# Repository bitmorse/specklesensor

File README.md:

# specklesensor
A photodiode array for laser speckle sensing and vibrometry.

Read the full paper [here](docs/thesis.pdf).

Spectral analysis of a 133 Hz surface vibration under different laser configurations. Top: Power spectral density showing the target frequency
component. Bottom: SNR improvement with increasing number of active lasers:

## RPI Camera Bench Setup

Side by side comparison of the speckle pattern captured by a Raspberry Pi camera with
one red laser

and three red lasers.

## Laser setups

## Hardware
The PCBs used for the experiments are in the `hardware` folder. The PCBs are designed using KiCad, an open source schematics and layout editor. The PCBs were manufactured by JLCPCB and hand assembled using hot air reflow.

- `speckle_pcb_rev1`: The 3x3 photodiode array.
- `speckle_amp_pcb_rev1`: The amplifier PCB for 3x3 array.

Careful attention must be paid to cleaning the PCBs after soldering, as any residue flux can lead to leakage currents and noise in the measurements.

## Scripts
- `emulations`: The script to process camera frames to CSV files for emulating the photodiode array. A notebook provides the signal processing.
- `waveshare`: Scripts for testing the first ADC.
- `daqhat`: Scripts for testing the second ADC and data from the multi-laser experiment.

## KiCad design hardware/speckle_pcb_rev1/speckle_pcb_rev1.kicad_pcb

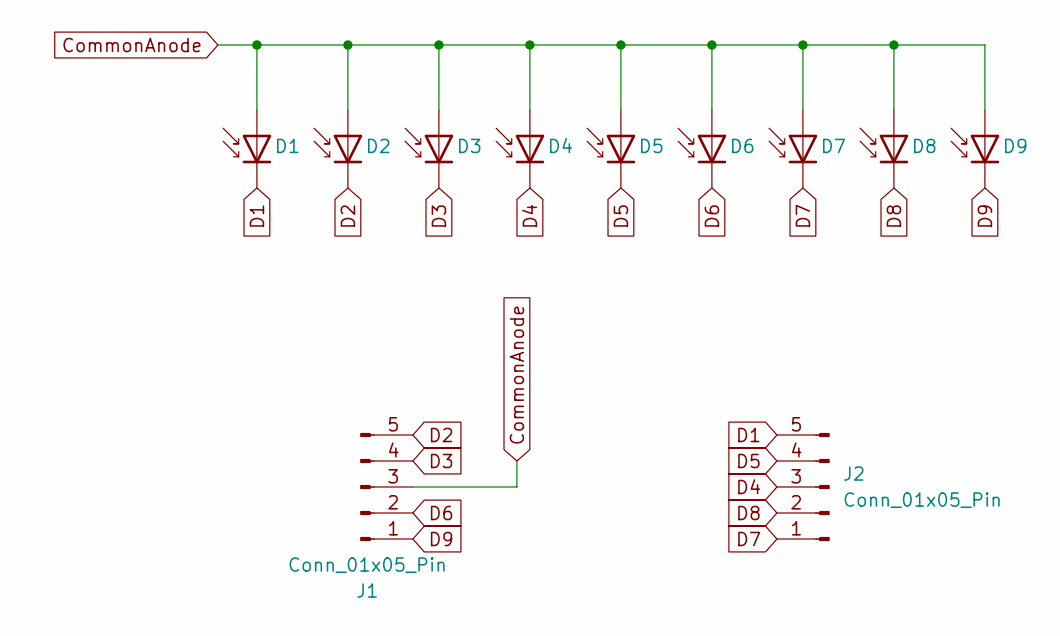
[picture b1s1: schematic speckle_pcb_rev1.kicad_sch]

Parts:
D1, D2, D3, D4, D5, D6, D7, D8, D9: D_Photo; VEMD2704
J1, J2: Conn_01x05_Pin; PinHeader_1x05_P1.27mm_Vertical

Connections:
CommonAnode: D1.2 (A), D2.2 (A), D3.2 (A), D4.2 (A), D5.2 (A), D6.2 (A), D7.2 (A), D8.2 (A), D9.2 (A), J1.3
D1: D1.1 (K), J2.5
D2: D2.1 (K), J1.5
D3: D3.1 (K), J1.4
D4: D4.1 (K), J2.3
D5: D5.1 (K), J2.4
D6: D6.1 (K), J1.2
D7: D7.1 (K), J2.1
D8: D8.1 (K), J2.2
D9: D9.1 (K), J1.1

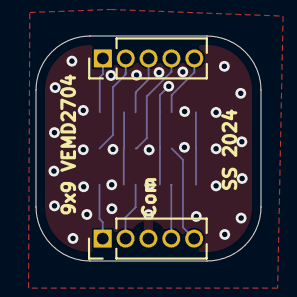
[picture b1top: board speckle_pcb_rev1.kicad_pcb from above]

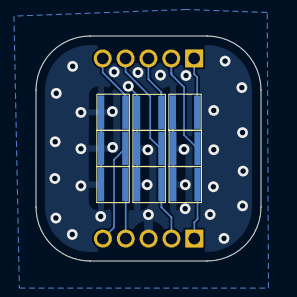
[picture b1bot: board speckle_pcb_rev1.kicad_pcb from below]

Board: 2 copper layers, 12.5 x 12.5 mm, 11 parts (9 on the bottom side), 10 nets.

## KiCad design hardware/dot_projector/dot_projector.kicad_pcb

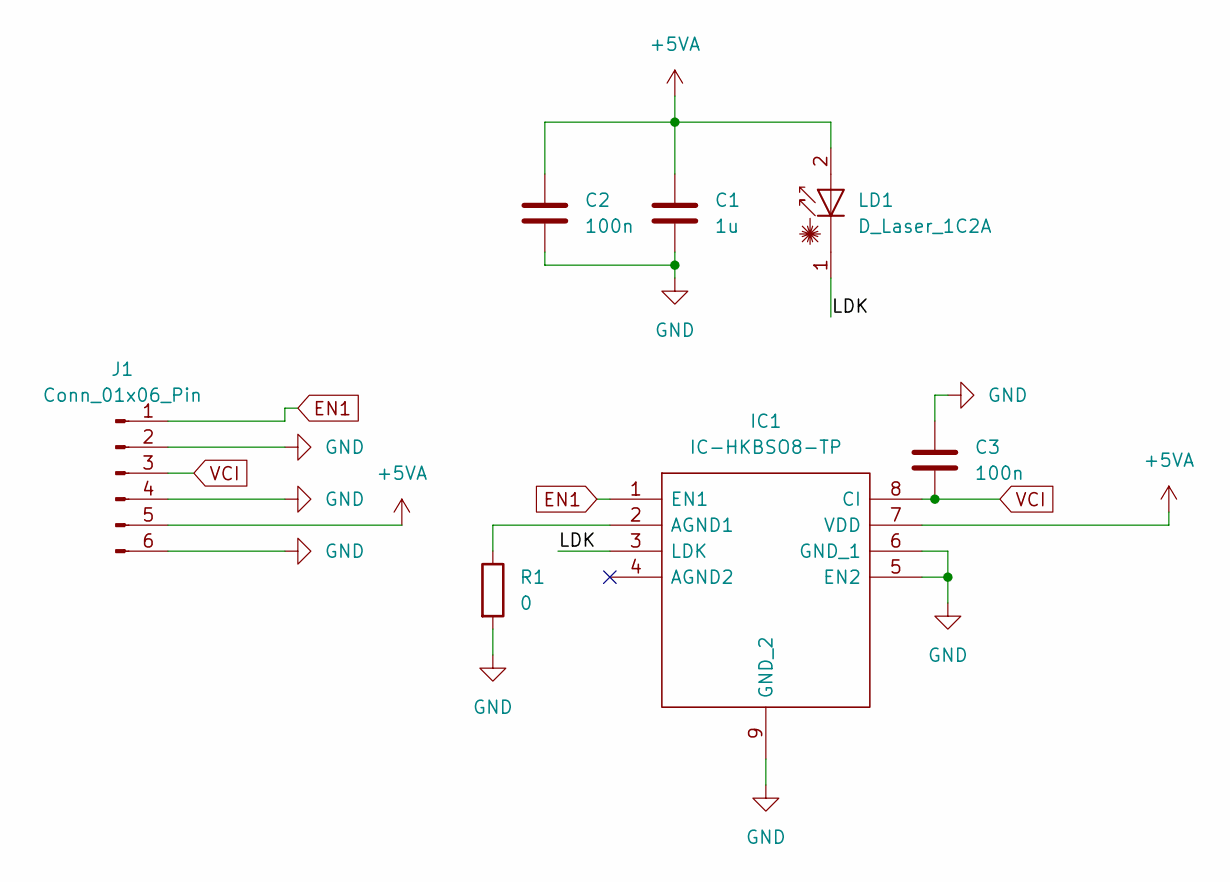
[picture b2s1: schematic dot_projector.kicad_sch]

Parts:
C1: 1u; C_0603_1608Metric
C2, C3: 100n; C_0603_1608Metric
IC1: IC-HKBSO8-TP; SOIC127P600X148-9N; Manufacturer_Part_Number IC-HKBSO8-TP
J1: Conn_01x06_Pin; PinHeader_1x06_P1.27mm_Vertical
LD1: D_Laser_1C2A; ams_belago1.1
R1: 0; R_0603_1608Metric

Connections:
+5VA: C1.1, C2.1, IC1.7 (VDD), J1.5, LD1.2 (A)
/LDK: IC1.3 (LDK), LD1.1 (K)
EN1: IC1.1 (EN1), J1.1
GND: C1.2, C2.2, C3.1, IC1.5 (EN2), IC1.6 (GND_1), IC1.9 (GND_2), J1.2, J1.4, J1.6, R1.2
unnamed: IC1.2 (AGND1), R1.1
VCI: C3.2, IC1.8 (CI), J1.3

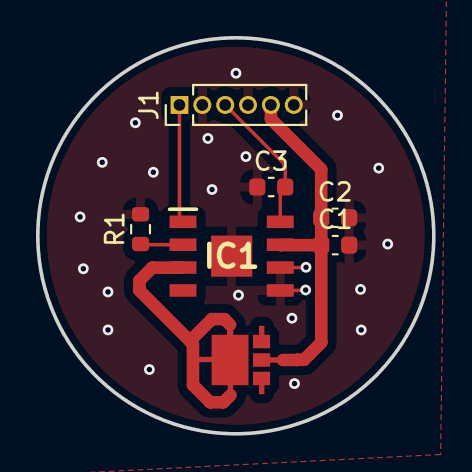
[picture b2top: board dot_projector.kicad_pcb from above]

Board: 2 copper layers, 22.0 x 22.0 mm, 7 parts (0 on the bottom side), 6 nets.

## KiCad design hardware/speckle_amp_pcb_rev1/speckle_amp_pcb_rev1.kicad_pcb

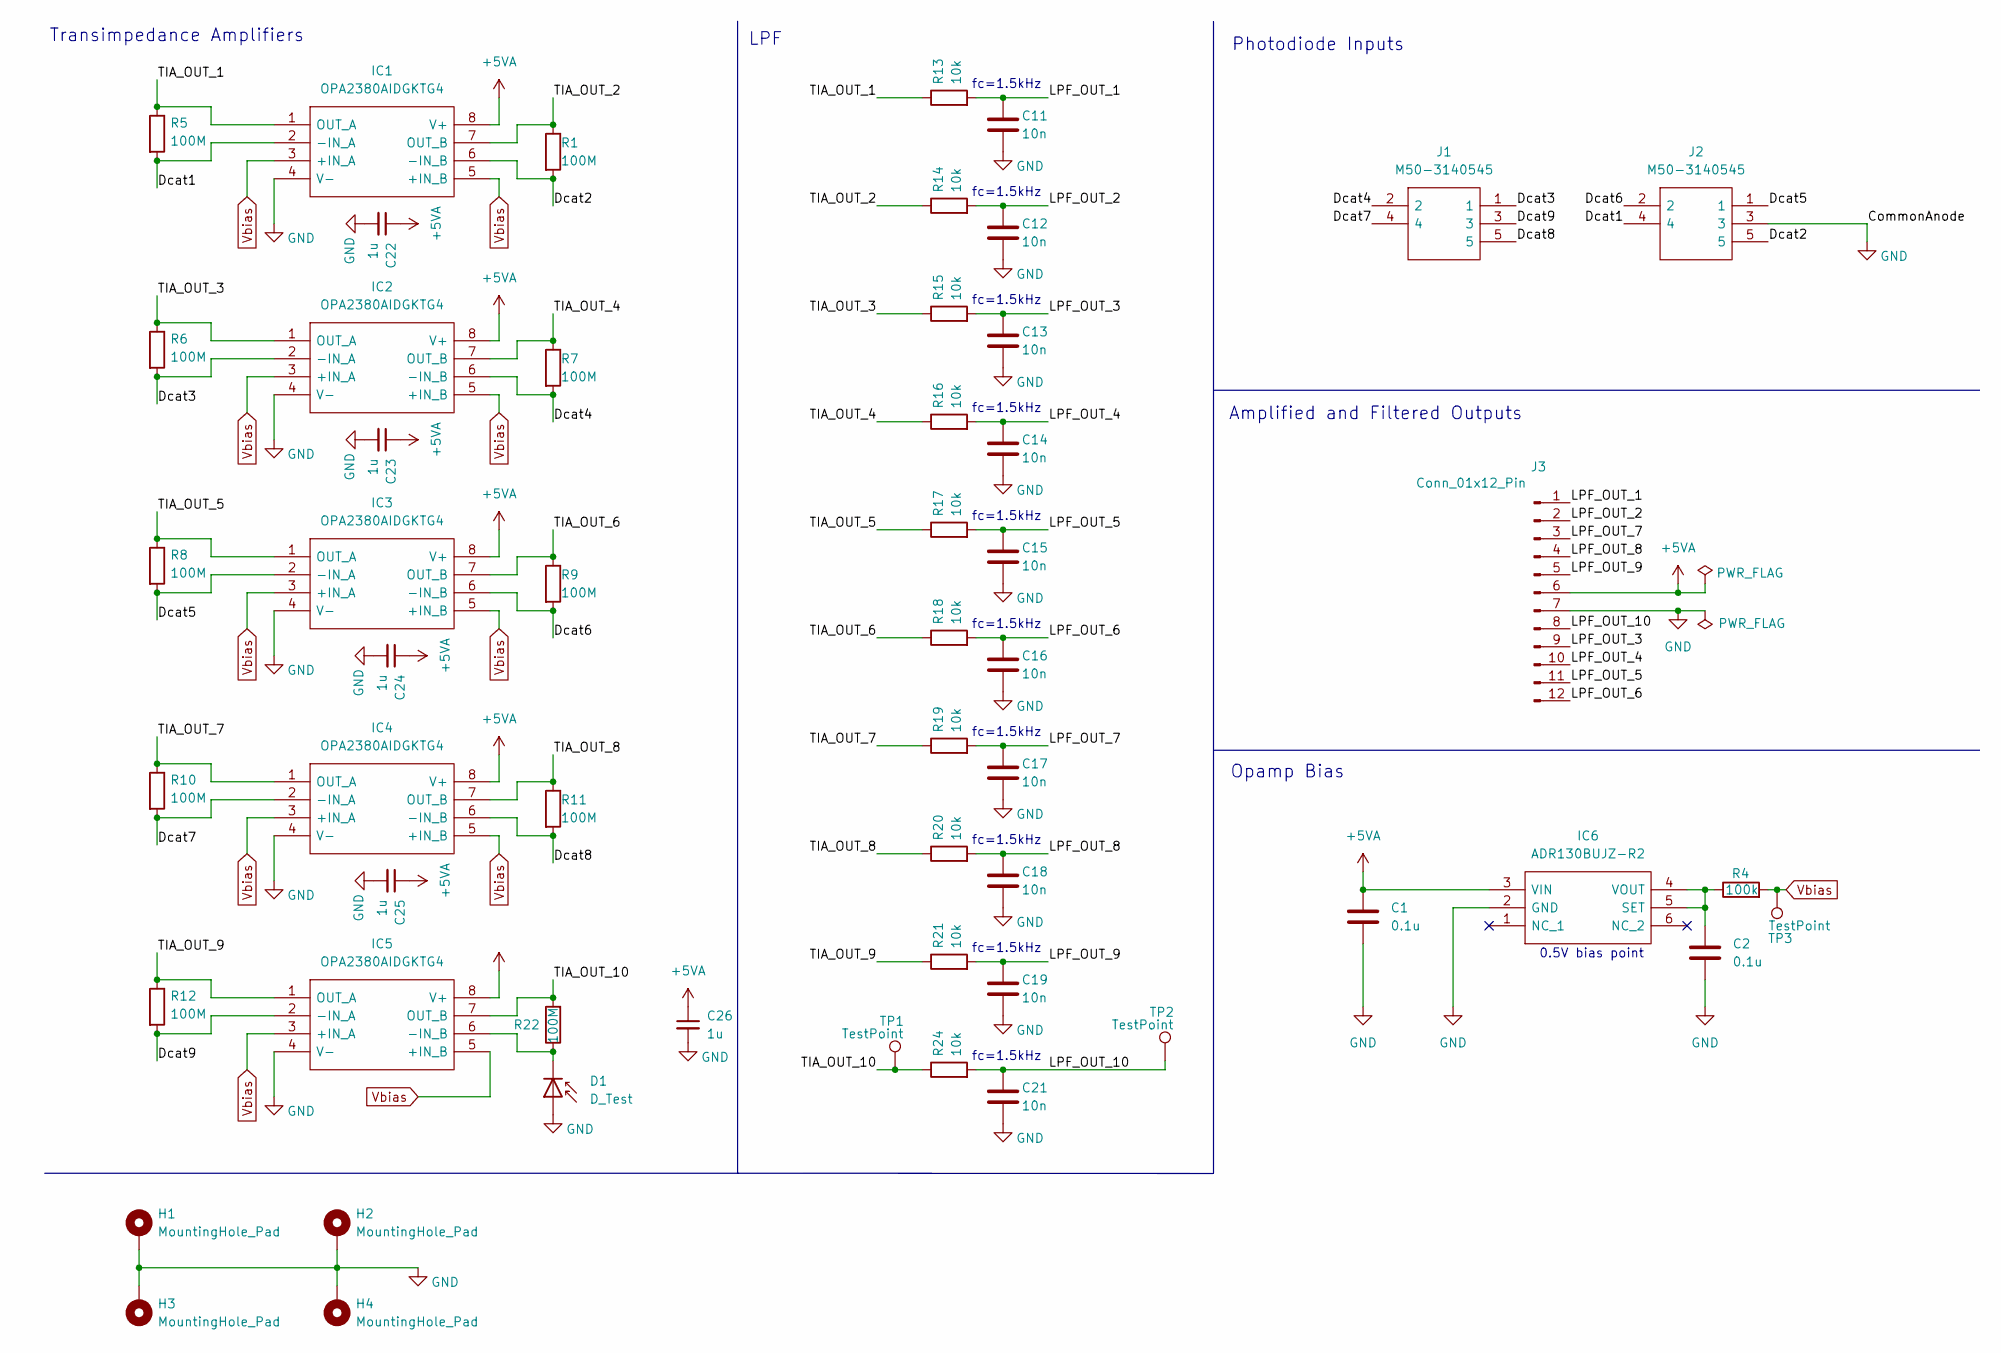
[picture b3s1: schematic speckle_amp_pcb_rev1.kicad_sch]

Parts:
C1, C2: 0.1u; C_0603_1608Metric
C11, C12, C13, C14, C15, C16, C17, C18, C19, C21: 10n; C_0603_1608Metric
C22, C23, C24, C25, C26: 1u; C_0603_1608Metric
D1: D_Test; VEMD2704
H1, H2, H3, H4: MountingHole_Pad; MountingHole_3.2mm_M3_DIN965_Pad
IC1, IC2, IC3, IC4, IC5: OPA2380AIDGKTG4; SOP65P490X110-8N; Manufacturer_Part_Number OPA2380AIDGKTG4; Mouser Part Number 595-OPA2380AIDGKTG4
IC6: ADR130BUJZ-R2; SOT95P280X100-6N; Manufacturer_Part_Number ADR130BUJZ-R2; Mouser Part Number 584-ADR130BUJZ-R2
J1, J2: M50-3140545; M503140545; Manufacturer_Part_Number M50-3140545; Mouser Part Number 855-M50-3140545
J3: Conn_01x12_Pin; PinHeader_1x12_P1.27mm_Horizontal
R1, R5, R6, R7, R8, R9, R10, R11, R12, R22: 100M; RESC3216X69N
R4: 100k; R_0603_1608Metric
R13, R14, R15, R16, R17, R18, R19, R20, R21, R24: 10k; R_0603_1608Metric
TP1, TP2, TP3: TestPoint; TestPoint_Pad_D1.0mm

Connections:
+5VA: C1.1, C22.1, C23.1, C24.1, C25.1, C26.1, IC1.8 (V+), IC2.8 (V+), IC3.8 (V+), IC4.8 (V+), IC5.8 (V+), IC6.3 (VIN), J3.6
/Dcat1: IC1.2 (-IN_A), J2.4, R5.2
/Dcat2: IC1.6 (-IN_B), J2.5, R1.2
/Dcat3: IC2.2 (-IN_A), J1.1, R6.2
/Dcat4: IC2.6 (-IN_B), J1.2, R7.2
/Dcat5: IC3.2 (-IN_A), J2.1, R8.2
/Dcat6: IC3.6 (-IN_B), J2.2, R9.2
/Dcat7: IC4.2 (-IN_A), J1.4, R10.2
/Dcat8: IC4.6 (-IN_B), J1.5, R11.2
/Dcat9: IC5.2 (-IN_A), J1.3, R12.2
/LPF_OUT_1: C11.1, J3.1, R13.2
/LPF_OUT_2: C12.1, J3.2, R14.2
/LPF_OUT_3: C13.1, J3.9, R15.2
/LPF_OUT_4: C14.1, J3.10, R16.2
/LPF_OUT_5: C15.1, J3.11, R17.2
/LPF_OUT_6: C16.1, J3.12, R18.2
/LPF_OUT_7: C17.1, J3.3, R19.2
/LPF_OUT_8: C18.1, J3.4, R20.2
/LPF_OUT_9: C19.1, J3.5, R21.2
/LPF_OUT_10: C21.1, J3.8, R24.2, TP2.1
/TIA_OUT_1: IC1.1 (OUT_A), R5.1, R13.1
/TIA_OUT_2: IC1.7 (OUT_B), R1.1, R14.1
/TIA_OUT_3: IC2.1 (OUT_A), R6.1, R15.1
/TIA_OUT_4: IC2.7 (OUT_B), R7.1, R16.1
/TIA_OUT_5: IC3.1 (OUT_A), R8.1, R17.1
/TIA_OUT_6: IC3.7 (OUT_B), R9.1, R18.1
/TIA_OUT_7: IC4.1 (OUT_A), R10.1, R19.1
/TIA_OUT_8: IC4.7 (OUT_B), R11.1, R20.1
/TIA_OUT_9: IC5.1 (OUT_A), R12.1, R21.1
/TIA_OUT_10: IC5.7 (OUT_B), R22.2, R24.1, TP1.1
GND: C1.2, C2.2, C11.2, C12.2, C13.2, C14.2, C15.2, C16.2, C17.2, C18.2, C19.2, C21.2, C22.2, C23.2, C24.2, C25.2, C26.2, D1.2 (A), H1.1, H2.1, H3.1, H4.1, IC1.4 (V-), IC2.4 (V-), IC3.4 (V-), IC4.4 (V-), IC5.4 (V-), IC6.2 (GND), J2.3, J3.7
unnamed: D1.1 (K), IC5.6 (-IN_B), R22.1
unnamed: C2.1, IC6.4 (VOUT), IC6.5 (SET), R4.1
Vbias: IC1.3 (+IN_A), IC1.5 (+IN_B), IC2.3 (+IN_A), IC2.5 (+IN_B), IC3.3 (+IN_A), IC3.5 (+IN_B), IC4.3 (+IN_A), IC4.5 (+IN_B), IC5.3 (+IN_A), IC5.5 (+IN_B), R4.2, TP3.1

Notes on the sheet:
LPF
fc=1.5kHz
Amplified and Filtered Outputs
Transimpedance Amplifiers
0.5V bias point
Photodiode Inputs
Opamp Bias

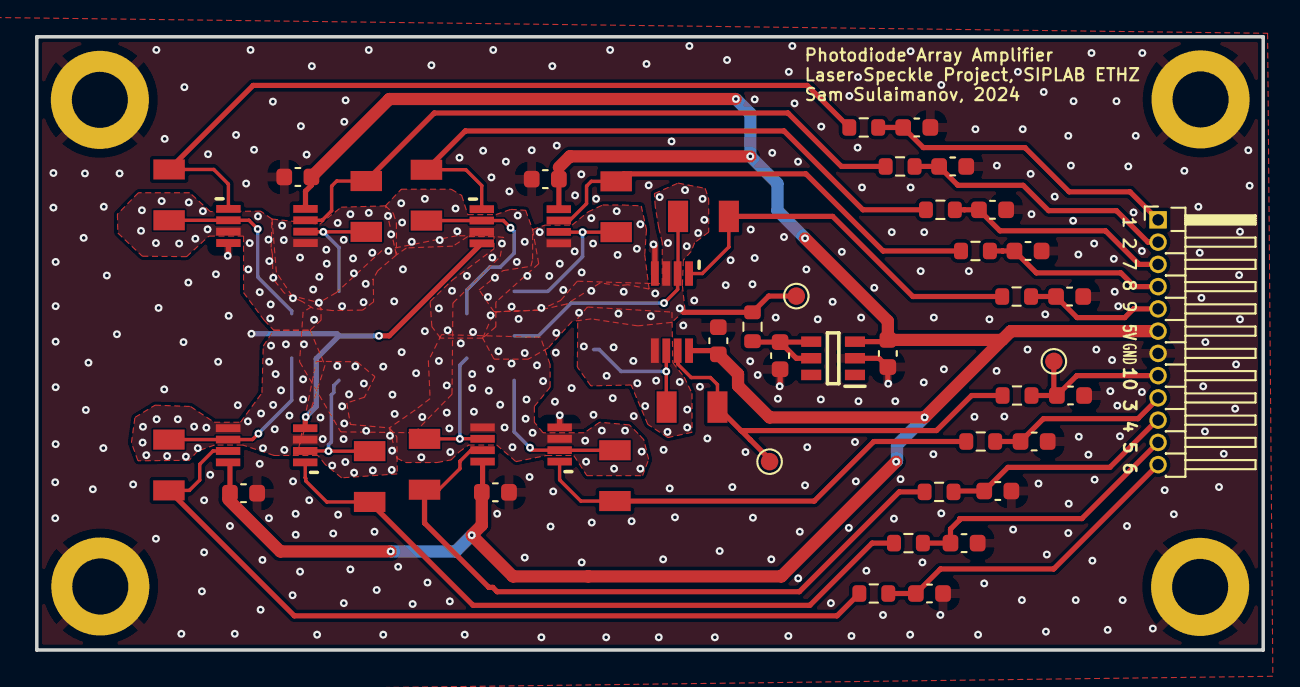
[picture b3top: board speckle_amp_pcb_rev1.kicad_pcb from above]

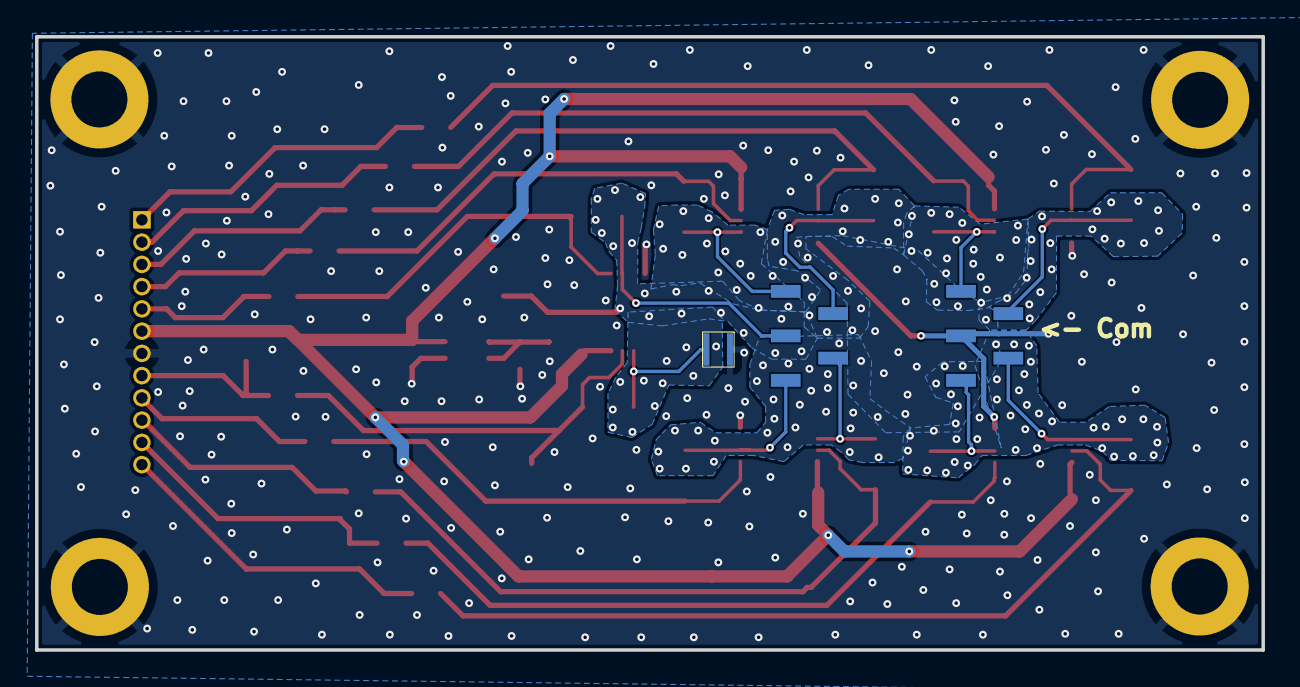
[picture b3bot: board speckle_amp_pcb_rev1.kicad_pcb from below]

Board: 2 copper layers, 70.0 x 35.0 mm, 55 parts (3 on the bottom side), 34 nets.

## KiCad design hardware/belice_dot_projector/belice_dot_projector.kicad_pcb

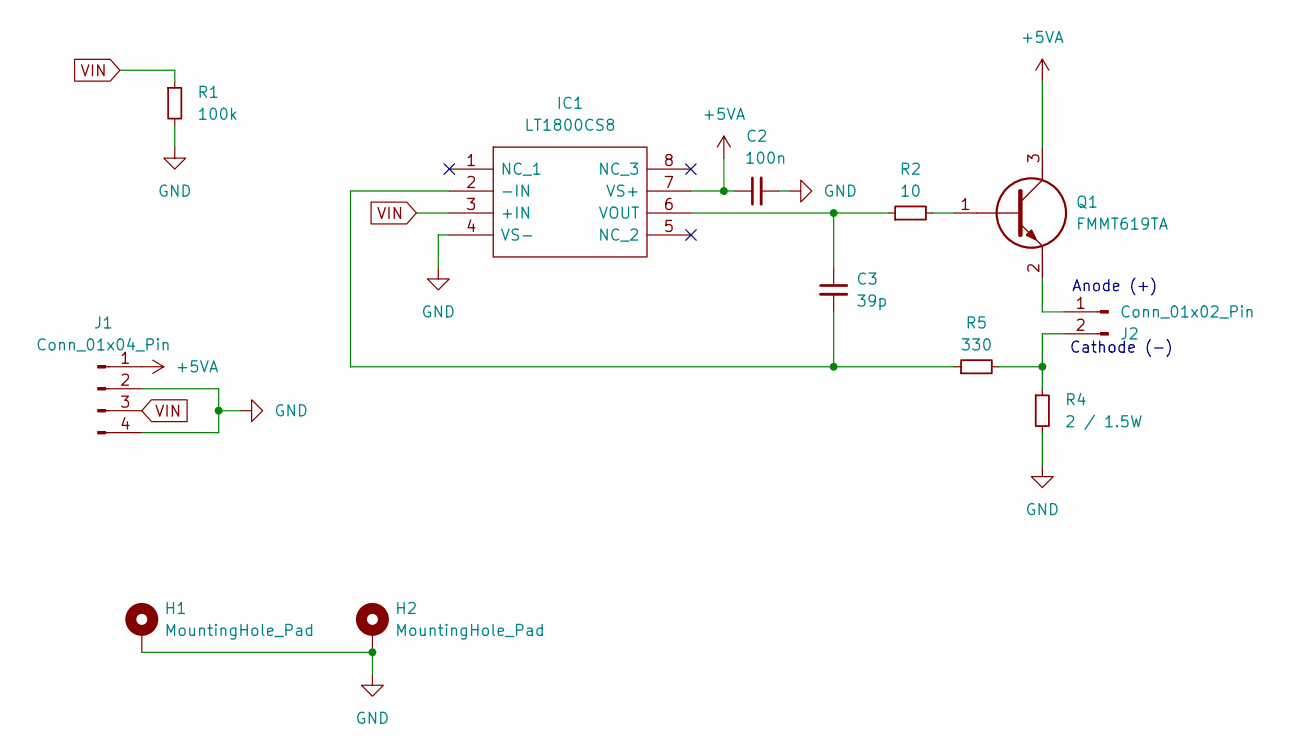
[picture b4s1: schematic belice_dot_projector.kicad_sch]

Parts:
C2: 100n; C_0603_1608Metric
C3: 39p; C_0603_1608Metric
H1, H2: MountingHole_Pad; MountingHole_3.2mm_M3_DIN965_Pad
IC1: LT1800CS8; SOIC127P599X175-8N; Manufacturer_Part_Number LT1800CS8
J1: Conn_01x04_Pin; PinHeader_1x04_P1.27mm_Vertical
J2: Conn_01x02_Pin; APDE-00
Q1: FMMT619TA; SOT95P237X112-3N; Manufacturer_Part_Number FMMT619TA; Mouser Part Number 522-FMMT619TA
R1: 100k; R_0603_1608Metric
R2: 10; R_0603_1608Metric
R4: 2 / 1.5W; R_2512_6332Metric
R5: 330; R_0603_1608Metric

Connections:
+5VA: C2.1, IC1.7 (VS+), J1.1, Q1.3
GND: C2.2, H1.1, H2.1, IC1.4 (VS-), J1.2, J1.4, R1.2, R4.2
unnamed: C3.2, IC1.2 (-IN), R5.1
unnamed: C3.1, IC1.6 (VOUT), R2.1
unnamed: J2.1, Q1.2
unnamed: J2.2, R4.1, R5.2
unnamed: Q1.1, R2.2
VIN: IC1.3 (+IN), J1.3, R1.1

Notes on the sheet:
Cathode (-)
Anode (+)

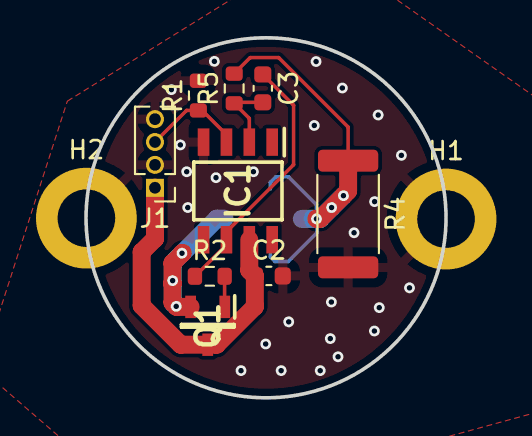
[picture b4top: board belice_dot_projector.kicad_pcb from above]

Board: 2 copper layers, 20.0 x 20.0 mm, 12 parts (1 on the bottom side), 8 nets.

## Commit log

2025-01-09 add harware
2025-01-09 adding update
2025-01-09 adding draft
2025-01-09 fix graph
2025-01-09 adding draft final
2025-01-10 final commit with code
2025-01-10 adding compressed pdf
